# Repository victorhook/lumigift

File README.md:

# Lumigift

Glowing Christmas presents that dance to music. Each Lumigift is a small 3D-printed
box with four RGB LEDs, a radio and an AAA battery. A computer runs the show over
2.4 GHz radio: live telemetry from every box, firmware updates for all of them at
once in seconds, and light shows synced to the beat of a song.

## What's in here

| Path | What |
|---|---|
| `kicad/lumigift-rev-a/` | Gift PCB: STM32C011F6, 4× WS2812B, nRF24L01+ socket, AAA boost |
| `firmware/lumigift/` | Gift firmware in Rust: a 10 KiB write-protected radio bootloader + the app |
| `firmware/nrf24-usb-bridge/` | USB ⇄ nRF24 bridge dongle (STM32F103C8 + nRF24L01+PA/LNA), generic and reusable |
| `crates/` | Shared `no_std` crates: radio driver, bridge protocol, gift protocol, LED effects |
| `host/lumigift-core` | Radio link manager: polling, telemetry, discovery, OTA, simulator |
| `host/lumigift-audio` | Audio decoding, playback clock, beat/section/drop analysis, shows |
| `host/lumigift-stage` | Real-time 3D stage renderer (wgpu) |
| `host/lumigift-studio` | The desktop app |
| `host/lumigift-cli` | Command-line tool |
| `docs/` | [Architecture](docs/ARCHITECTURE.md) and [UI design](docs/UI_DESIGN.md) |

Everything is Rust. The radio driver and protocols are written from scratch, and the
LED effects are one crate that runs both on the gifts and in the 3D preview, so the
preview shows exactly what the hardware will do.

## Quick start (no hardware needed)

```sh
cargo run --release -p lumigift-studio -- --sim 10   # the app, with 10 simulated gifts
cargo run --release -p lumigift-cli -- --sim 10 scan # or the CLI
cargo run --release -p lumigift-stage --example demo # just the 3D stage
```

## With hardware

1. **Bridge dongle:** wire the nRF24 module to the F103 board, switch the board's
   USB-C data lines from the CH340 to PA11/PA12, add a 1.5 kΩ pull-up from PA12 to
   3V3 (the board has none: the CH340 had it built in), and flash it once with an
   ST-Link (`firmware/nrf24-usb-bridge/flash-swd.sh`). After that it updates over
   USB: `lumigift bridge-update <elf>`. See
   [`firmware/nrf24-usb-bridge/README.md`](firmware/nrf24-usb-bridge/README.md), which
   also has the udev rule.
2. **Gifts (once per board, over SWD):** `cd firmware/lumigift && cargo xtask flash`
   writes the bootloader and the app. See [`firmware/lumigift/README.md`](firmware/lumigift/README.md).
3. **From then on, update every gift over the air:**
   ```sh
   cd firmware/lumigift && cargo xtask image                # → target/lumigift-app.img
   cargo run --release -p lumigift-cli -- ota firmware/lumigift/target/lumigift-app.img
   ```
   or drop the image into the Firmware page of the Studio.

## How it works

* **Radio link:** the bridge broadcasts a show frame 100 times a second, carrying a
  timestamp that keeps every gift's clock locked to the bridge. Between frames it
  polls each gift, and the gift answers inside the hardware ack with uptime,
  battery, link quality, reset reason and firmware version.
* **Firmware update:** a reboot command drops the gifts into their bootloader. The
  image goes out as broadcast chunks to all of them at once, each gift reports
  what it missed, those chunks are resent, and each image is CRC-checked before it
  boots. A power cut mid-update just leaves the gift waiting in its bootloader.
* **Music:** a song is analysed up front (tempo, beats, bars, sections, drops). A
  show is a timeline of effect and palette cues, generated automatically and
  editable in the Studio. During playback the host sends compact music frames
  (band energies, beat phase and flags) a little ahead of the audio, so the gifts
  light up exactly in time with what you hear.

Details are in [docs/ARCHITECTURE.md](docs/ARCHITECTURE.md).

## Design

The PCB fits snugly in the 3D-printed box, and the lid snaps on tight enough to stay on.

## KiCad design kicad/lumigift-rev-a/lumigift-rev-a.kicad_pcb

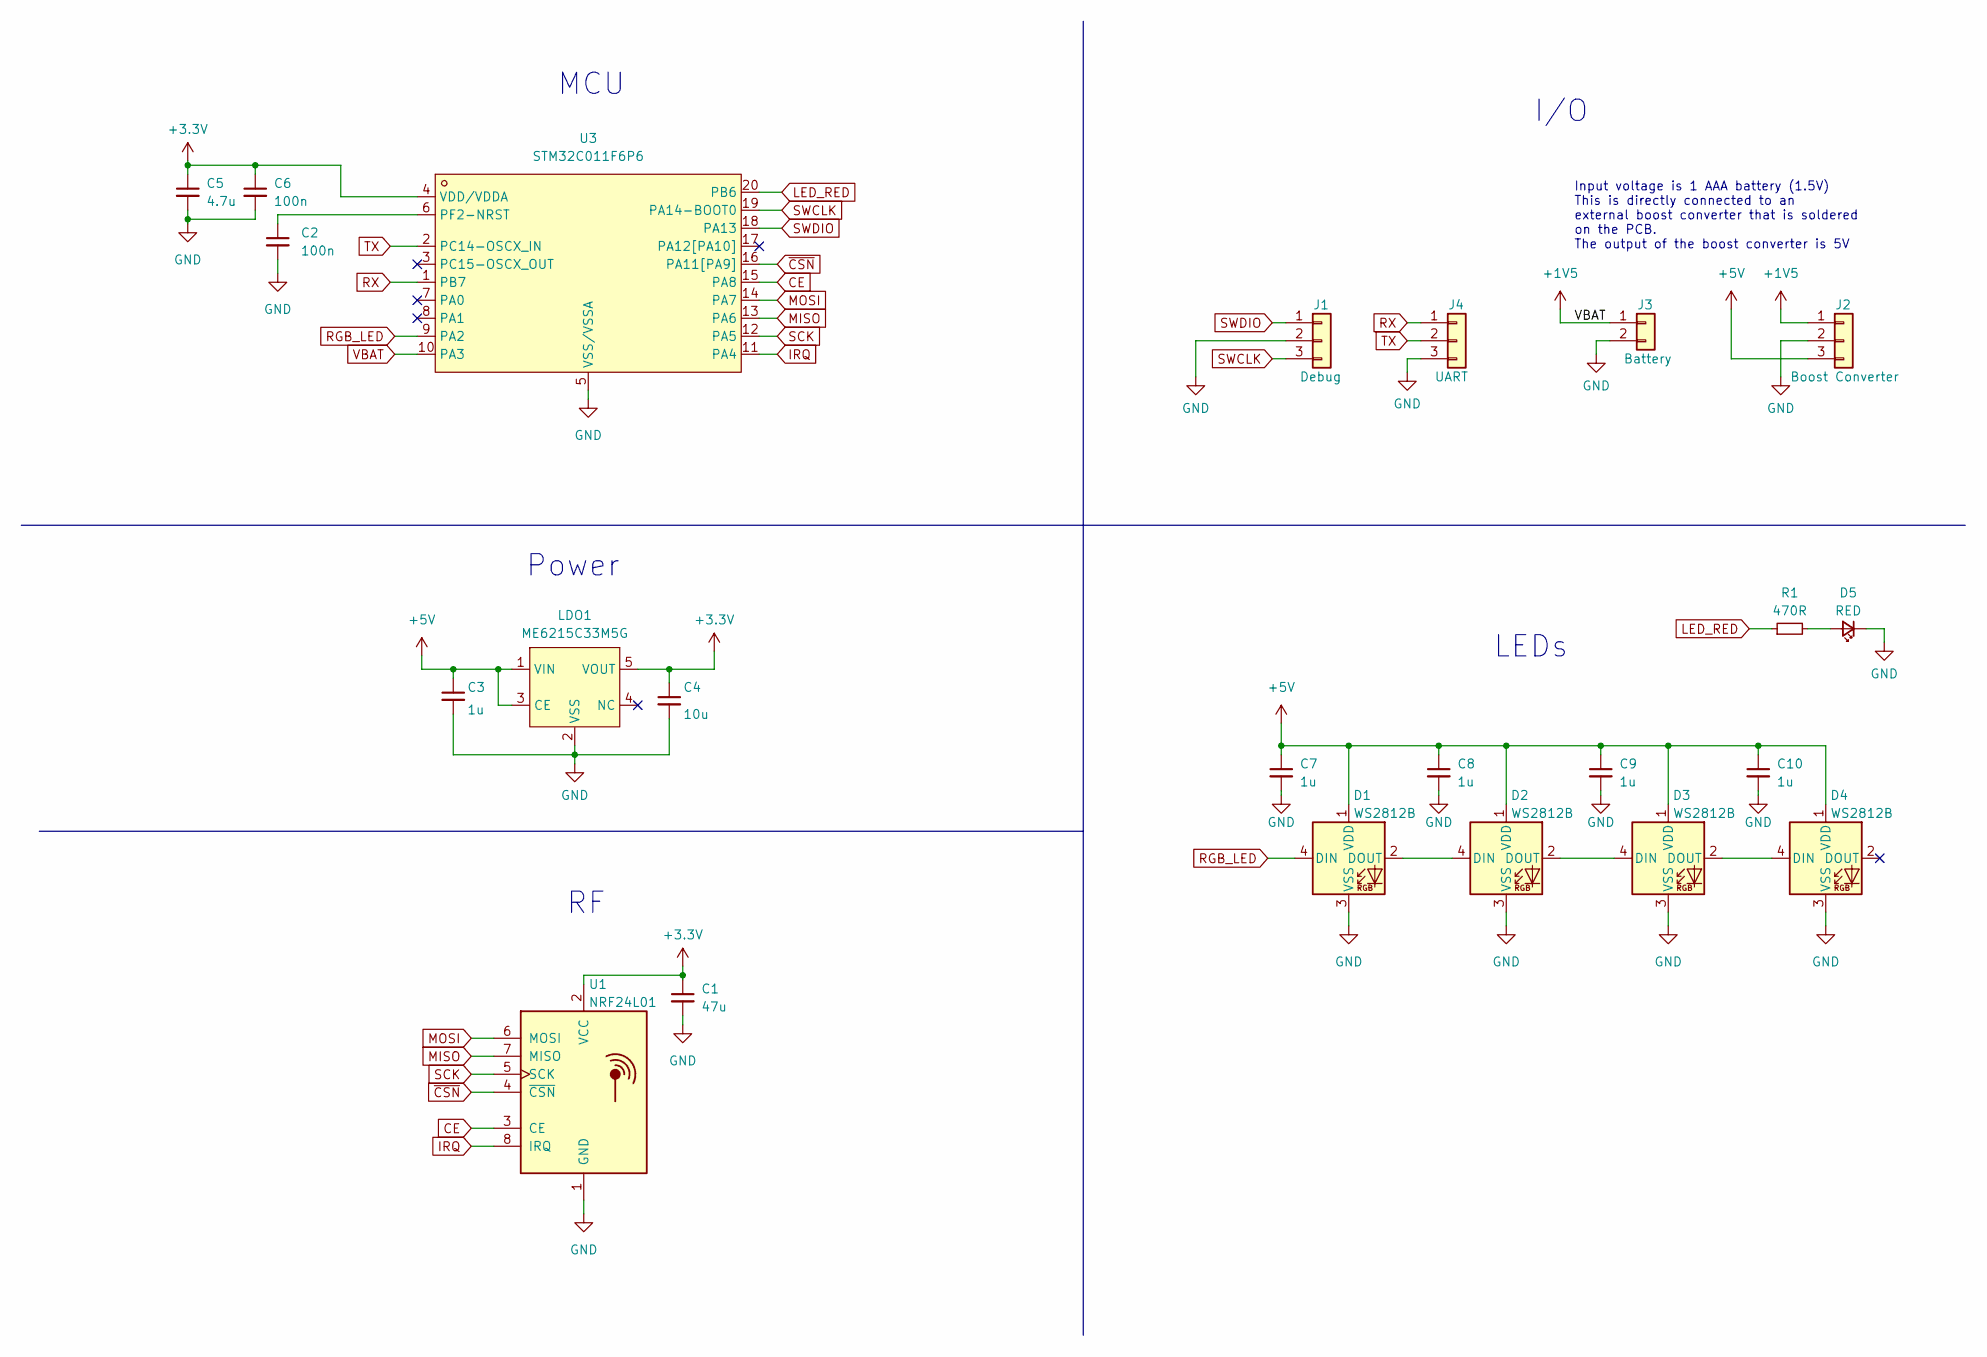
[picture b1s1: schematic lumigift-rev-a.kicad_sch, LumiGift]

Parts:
C1: 47u; C_1206_3216Metric
C2, C6: 100n; C_0402_1005Metric
C3, C7, C8, C9, C10: 1u; C_0402_1005Metric
C4: 10u; C_0805_2012Metric
C5: 4.7u; C_0805_2012Metric
D1, D2, D3, D4: WS2812B; LED_WS2812B_PLCC4_5.0x5.0mm_P3.2mm_No_Silk
D5: RED; LED_0603_1608Metric
J1: Debug; PinHeader_1x03_P2.54mm_Vertical_SMD_Pin1Left; MPN C5160786
J2: Boost Converter; PinHeader_1x03_P2.54mm_Vertical
J3: Battery; AAA_Battery_Holder
J4: UART; PinHeader_1x03_P2.54mm_Vertical_SMD_Pin1Left; MPN C5160786
LDO1: ME6215C33M5G; SOT-23-5_L3.0-W1.7-P0.95-LS2.8-BR; LCSC Part C84119
R1: 470R; R_0402_1005Metric
U1: NRF24L01; HDR-SMD_8P-P2.54-V-F-R2-C4-S7.1; MPN C3975149
U3: STM32C011F6P6; TSSOP-20_L6.5-W4.4-P0.65-LS6.4-BL; LCSC Part C5456198

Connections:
+3.3V: C1.1, C4.1, C5.1, C6.1, LDO1.5 (VOUT), U1.2 (VCC), U3.4 (VDD/VDDA)
+5V: C3.1, C7.1, C8.1, C9.1, C10.1, D1.1 (VDD), D2.1 (VDD), D3.1 (VDD), D4.1 (VDD), J2.3, LDO1.1 (VIN), LDO1.3 (CE)
CE: U1.3 (CE), U3.15 (PA8)
GND: C1.2, C2.2, C3.2, C4.2, C5.2, C6.2, C7.2, C8.2, C9.2, C10.2, D1.3 (VSS), D2.3 (VSS), D3.3 (VSS), D4.3 (VSS), D5.1 (K), J1.2, J2.2, J3.2, J4.3, LDO1.2 (VSS), U1.1 (GND), U3.5 (VSS/VSSA)
IRQ: U1.8 (IRQ), U3.11 (PA4)
LED_RED: R1.1, U3.20 (PB6)
MISO: U1.7 (MISO), U3.13 (PA6)
MOSI: U1.6 (MOSI), U3.14 (PA7)
unnamed: D1.2 (DOUT), D2.4 (DIN)
unnamed: D2.2 (DOUT), D3.4 (DIN)
unnamed: D3.2 (DOUT), D4.4 (DIN)
unnamed: D5.2 (A), R1.2
unnamed: C2.1, U3.6 (PF2-NRST)
RGB_LED: D1.4 (DIN), U3.9 (PA2)
RX: J4.1, U3.1 (PB7)
SCK: U1.5 (SCK), U3.12 (PA5)
SWCLK: J1.3, U3.19 (PA14-BOOT0)
SWDIO: J1.1, U3.18 (PA13)
TX: J4.2, U3.2 (PC14-OSCX_IN)
VBAT: J2.1, J3.1, U3.10 (PA3)
~CSN: U1.4 (~CSN), U3.16 (PA11[PA9])

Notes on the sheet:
Input voltage is 1 AAA battery (1.5V) This is directly connected to an external boost converter that is soldered on the PCB. The output of the boost converter is 5V
I/O
Power
MCU
LEDs

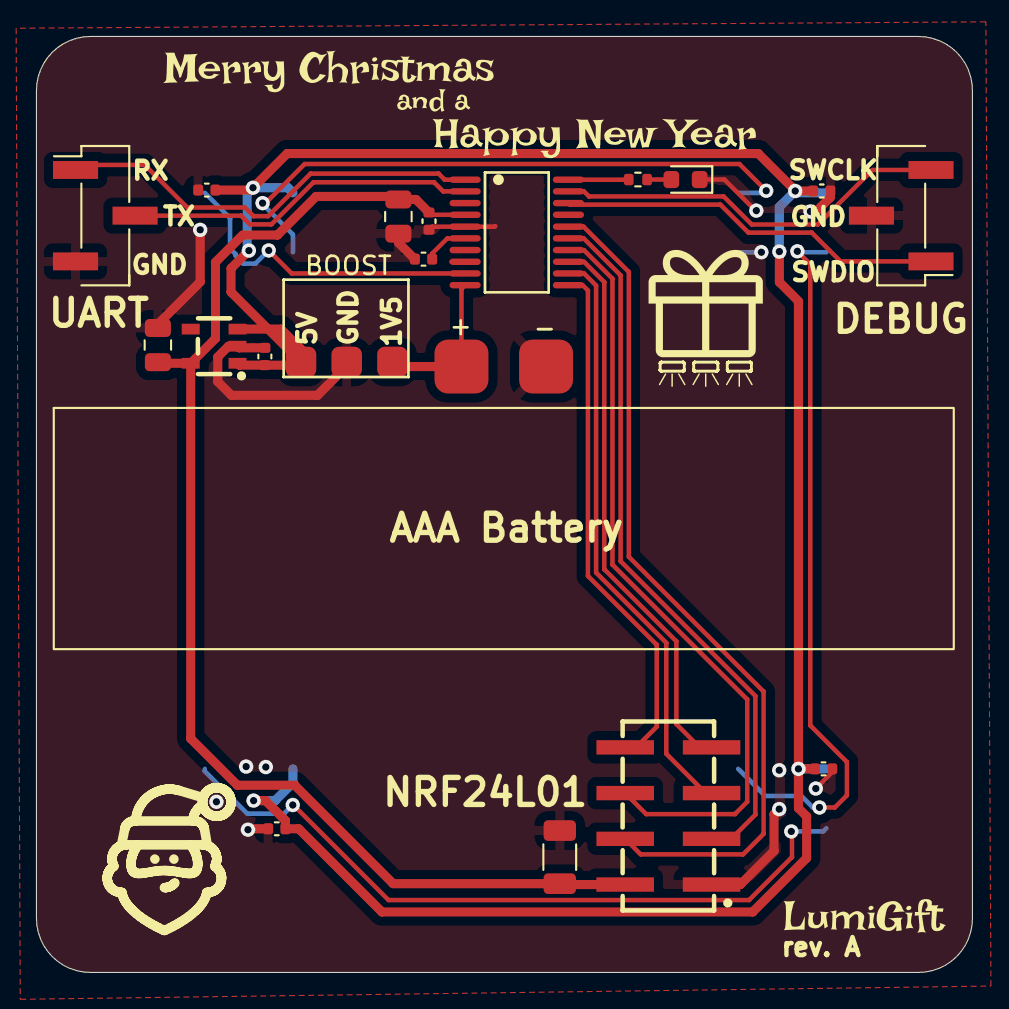
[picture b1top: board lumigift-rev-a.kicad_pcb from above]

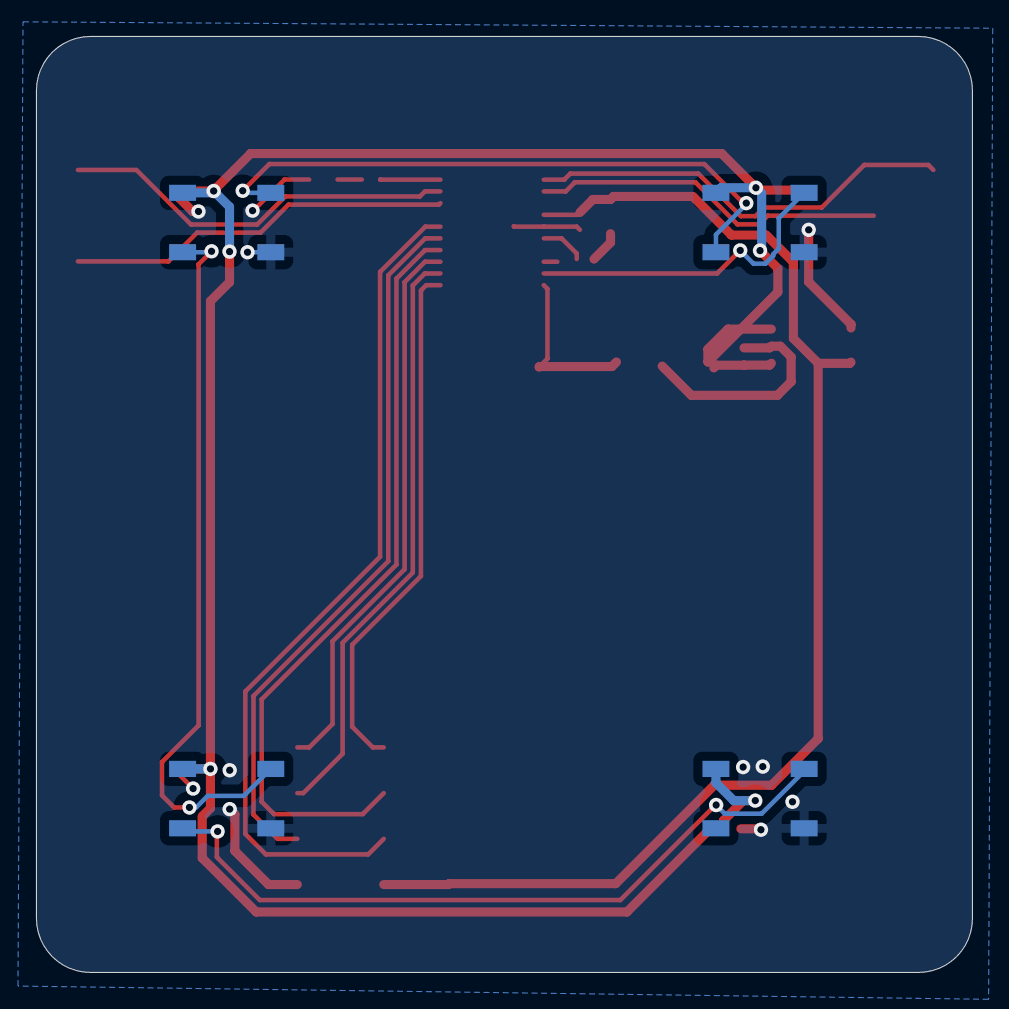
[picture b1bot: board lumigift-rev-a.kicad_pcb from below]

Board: 2 copper layers, 52.0 x 52.0 mm, 23 parts (4 on the bottom side), 21 nets.

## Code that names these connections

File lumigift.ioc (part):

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Mcu.Name=STM32C011F(4-6)Px
Mcu.Package=TSSOP20
Mcu.UserName=STM32C011F6Px
PA11\ [PA9].Signal=GPIO_Input
PA13.Mode=Serial_Wire
PA13.Signal=DEBUG_SWDIO
PA14-BOOT0.Mode=Serial_Wire
PA14-BOOT0.Signal=DEBUG_SWCLK
PA2.Signal=S_TIM1_CH3
PA3.Mode=IN3
PA3.Signal=ADC1_IN3
PA4.Signal=GPIO_Output
PA5.Signal=SPI1_SCK
PA6.Signal=SPI1_MISO
PA7.Signal=SPI1_MOSI
PA8.Signal=GPIO_Output
PB6.Signal=GPIO_Output
PB7.Signal=USART1_RX
PC14-OSCX_IN\ (PC14).Signal=USART1_TX
RCC.HSE_VALUE=8000000
RCC.SYSCLKFreq_VALUE=12000000
board=custom

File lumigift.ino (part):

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#include <EEPROM.h>


#define PIN_UART_RX PB7
#define PIN_UART_TX PC14
#define PIN_RGB_LED PA2
#define PIN_LED PB6
#define PIN_VBAT PA3
#define PIN_CSN PA11
#define PIN_CE PA8
#define PIN_MOSI PA7
#define PIN_MISO PA6
#define PIN_SCK PA5
#define PIN_IRQ PA4

#define NUM_LEDS 4

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

// -- Variables -- //
static RF24 radio(PIN_CE, PIN_CSN);
static uint8_t rx_address[RADIO_ADDRESS_SIZE]  = {0x42, 0x42, 0x42, 0x42, 0x01};
static uint8_t tx_address[RADIO_ADDRESS_SIZE] = {0x42, 0x42, 0x42, 0x42, 0x01};
static color_packet_t color = {0, 0, 0};
Adafruit_NeoPixel pixels(NUM_LEDS, PIN_RGB_LED, NEO_GRB + NEO_KHZ800);

static uint8_t current_id = 0;
static uint32_t last_packet_received = 0;
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{
    // Initialize GPIO
    pinMode(PIN_LED, OUTPUT);
    pinMode(PIN_CSN, OUTPUT);
    pinMode(PIN_CE, OUTPUT);
    digitalWrite(PIN_LED, LOW);

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
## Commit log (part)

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2023-10-12 PCB Rev. A done
2023-12-04 Added firmware code
2023-12-04 Added python lib and flask webapp
2023-12-04 Added readme
2023-12-04 Updated gitignore
2023-12-04 Fixed name bug
2023-12-04 Updated README and added images
